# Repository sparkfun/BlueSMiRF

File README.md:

_**NOTE:** This version of the product has been retired from our catalog. However, we do have the [BlueSMIRF V2 with headers](https://www.sparkfun.com/products/23287) and the [BlueSMiRF V2 PTH version available](https://www.sparkfun.com/products/24113)!_

_Please check out some of these resources to see how other users are still hacking and improving on this version of the product._

* [SparkFun Forum](https://forum.sparkfun.com/)
* [Comments Here on GitHub](https://github.com/sparkfun/BlueSMiRF/issues)

BlueSMiRF
=========

<table class="table table-hover table-striped table-bordered">
  <tr align="center">
   <td></td>
   <td></td>
  </tr>
  <tr align="center">
    <td><a href="https://www.sparkfun.com/products/12582">Bluetooth BlueSMiRF Gold: RN-41 Module (WRL-12582)</a></td>
    <td><a href="https://www.sparkfun.com/products/12577">Bluetooth Modem-BlueSMiRF Silver: RN-42 module (WRL-12577)</a></td>
  </tr>
</table>

These Bluetooth wireless modems work as a TTL serial (RX/TX) pipe, as a replacement for serial cable connections. 

Repository Contents
-------------------
* **/Hardware** - All Eagle design files (.brd, .sch)

Documentation
--------------
* **[Hookup Guide](https://learn.sparkfun.com/tutorials/using-the-bluesmirf)** - Basic hookup guide for the BlueSMiRF and Bluetooth Mate.
* **[SparkFun 3D Model repo](https://github.com/sparkfun/3D_Models)** - 3D models of SparkFun products. 

Current Product Versions
------------------------
* [WRL-12582](https://www.sparkfun.com/products/12582)- BlueSMiRF Gold: RN-41 Module
* [WRL-12577](https://www.sparkfun.com/products/12577)- BlueSMiRF Silver: RN-42 Module

Retired Product Versions
------------------------
* [WRL-10269](https://www.sparkfun.com/products/10269)- BlueSMiRF Silver: RN-42 Module
* [WRL-10268](https://www.sparkfun.com/products/10268)- BlueSMiRF Gold: RN-41 Module v16
* [WRL-10938](https://www.sparkfun.com/products/10938)- BlueSMiRF HID: RN-42 module loaded with Human Interface Device firmware

License Information
-------------------
The hardware is released under [Creative Commons Share-alike 3.0](http://creativecommons.org/licenses/by-sa/3.0/).

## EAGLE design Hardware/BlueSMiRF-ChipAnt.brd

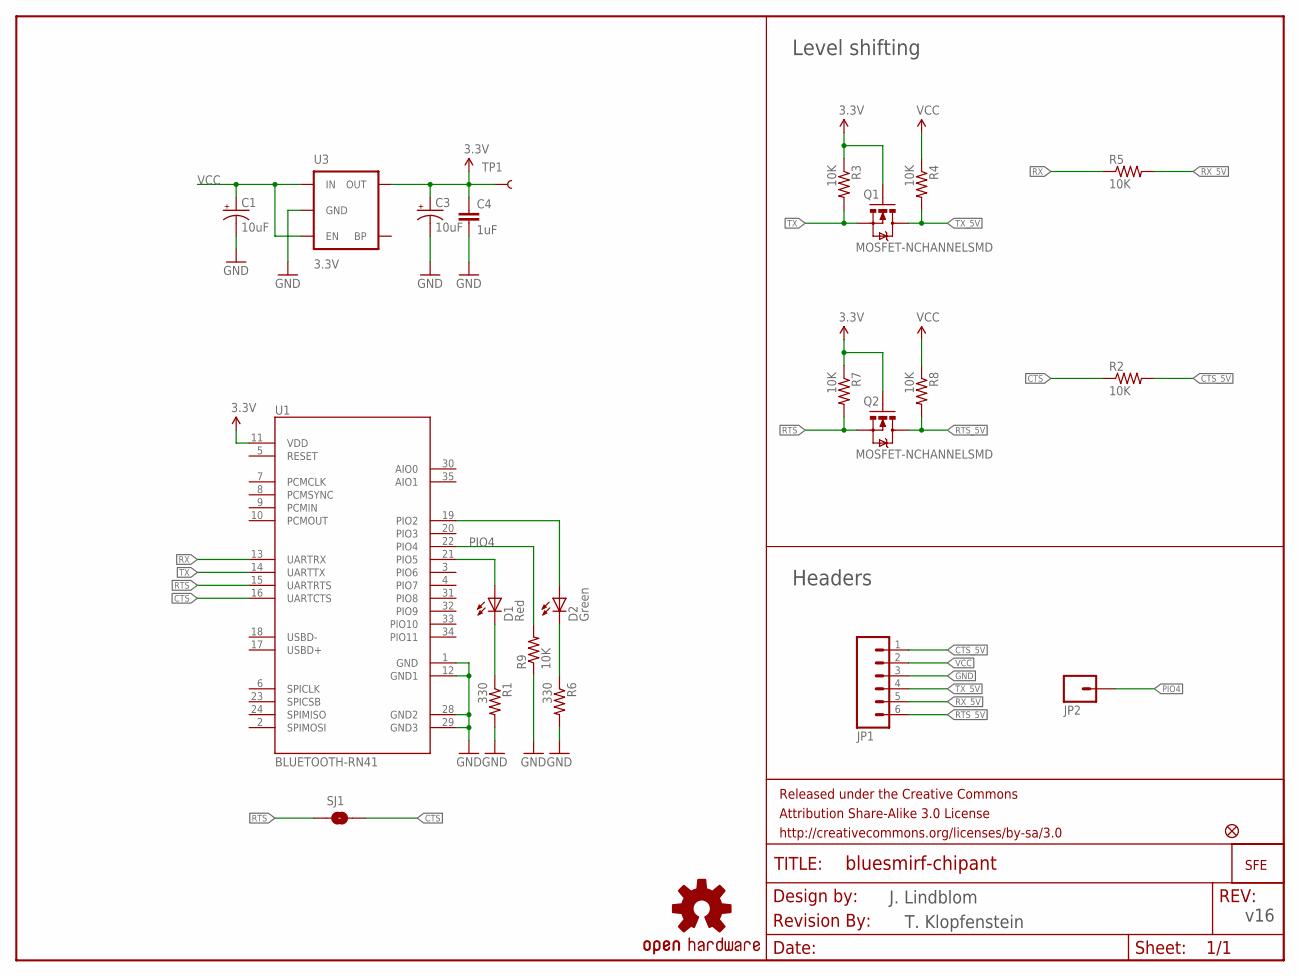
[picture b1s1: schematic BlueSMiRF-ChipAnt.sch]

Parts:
C1, C3: 10uF; EIA3216
C4: 1uF; 0603-CAP
D1: Red; LED-0603
D2: Green; LED-0603
FRAME1: FRAME-LETTER; CREATIVE_COMMONS
JP1: M06SIP; 1X06
JP2: M01SMDNS; 1X01NS
JP4: FIDUCIAL1X2; FIDUCIAL-1X2
LOGO1: OSHW-LOGOS; OSHW-LOGO-S
Q1, Q2: MOSFET-NCHANNELSMD; SOT23-3
R1, R6: 330; 0603-RES
R2, R3, R4, R5, R7, R8, R9: 10K; 0603-RES
SJ1: SOLDERJUMPERNO; SJ_2S-NO
TP1: TEST-POINT3X5; PAD.03X.05
U1: BLUETOOTH-RN41; RN41
U3: 3.3V; SOT23-5
U$1: LOGO-SFENEW; SFE-NEW-WEBLOGO
U$2: REVISION

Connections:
3.3V: C3.A (+), C4.1, Q1.1 (G), Q2.1 (G), R3.1, R7.1, TP1.P$1, U1.11 (VDD), U3.5 (OUT)
CTS: R2.1, SJ1.2, U1.16 (UARTCTS)
CTS_5V: JP1.1, R2.2
D1: D1.C, R1.1
D2: D2.C, R6.1
GND: C1.C (-), C3.C (-), C4.2, JP1.3, R1.2, R6.2, R9.1, U1.1 (GND), U1.12 (GND1), U1.28 (GND2), U1.29 (GND3), U3.2 (GND)
unnamed: D1.A, U1.21 (PIO5)
unnamed: D2.A, U1.19 (PIO2)
PIO4: JP2.1, R9.2, U1.22 (PIO4)
RTS: Q2.2 (S), R7.2, SJ1.1, U1.15 (UARTRTS)
RTS_5V: JP1.6, Q2.3 (D), R8.2
RX: R5.1, U1.13 (UARTRX)
RX_5V: JP1.5, R5.2
TX: Q1.2 (S), R3.2, U1.14 (UARTTX)
TX_5V: JP1.4, Q1.3 (D), R4.2
VCC: C1.A (+), JP1.2, R4.1, R8.1, U3.1 (IN), U3.3 (EN)

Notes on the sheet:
Level shifting
Headers
J. Lindblom
v16
T. Klopfenstein

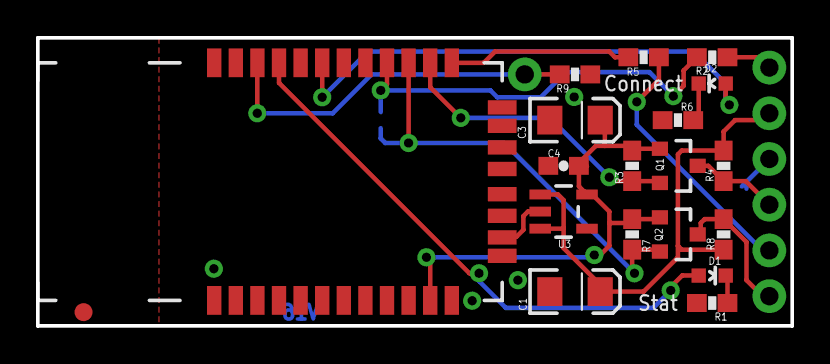
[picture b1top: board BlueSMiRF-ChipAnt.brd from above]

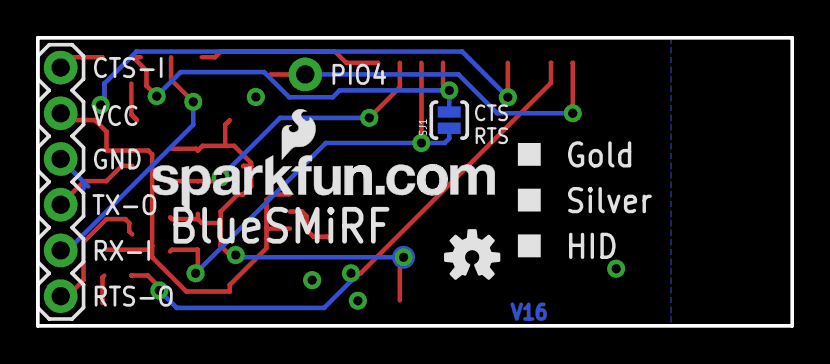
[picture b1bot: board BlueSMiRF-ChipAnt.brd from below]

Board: 2 copper layers, 41.9 x 16.0 mm, 27 parts (5 on the bottom side), 16 nets.

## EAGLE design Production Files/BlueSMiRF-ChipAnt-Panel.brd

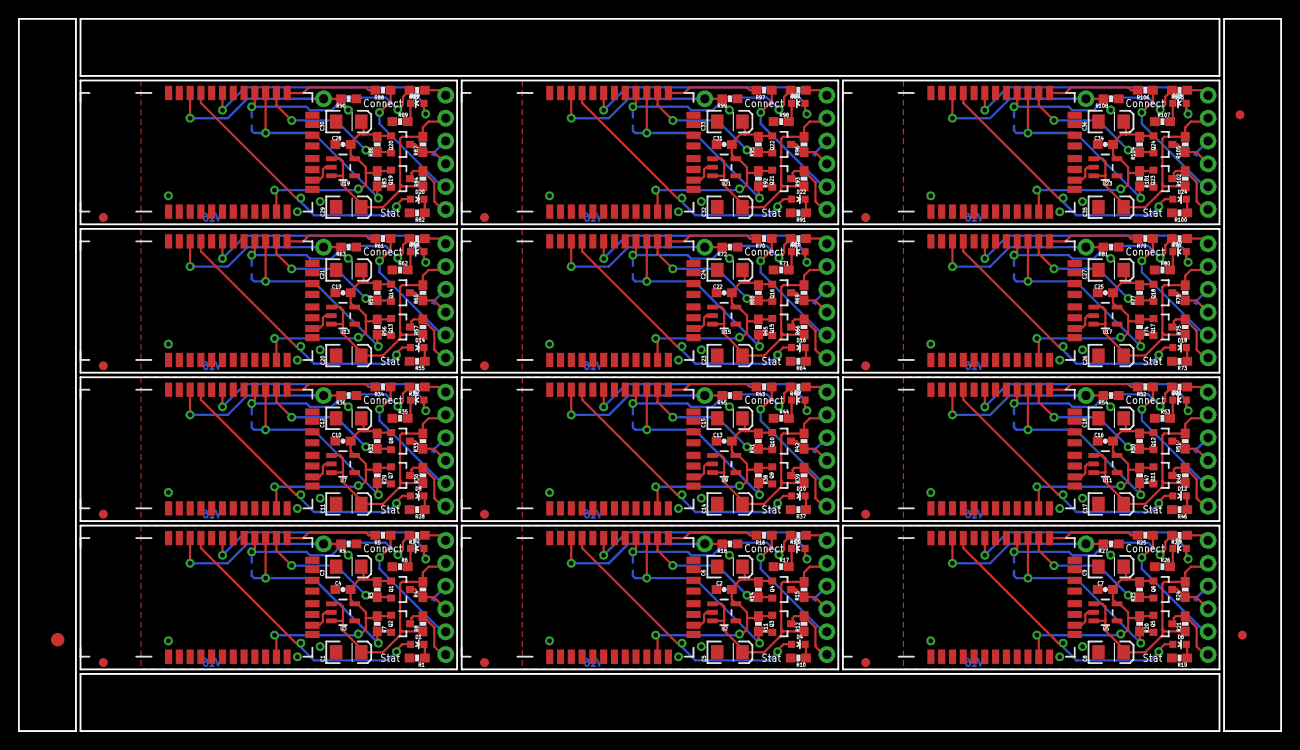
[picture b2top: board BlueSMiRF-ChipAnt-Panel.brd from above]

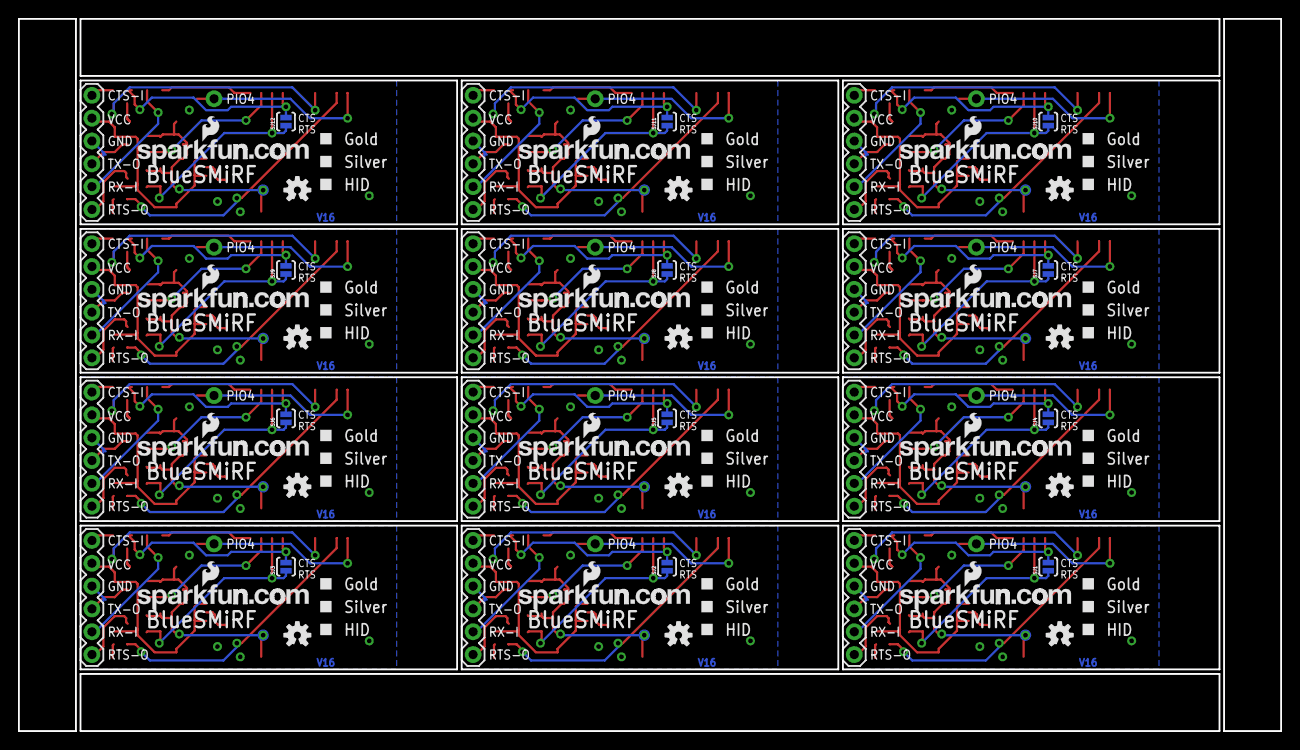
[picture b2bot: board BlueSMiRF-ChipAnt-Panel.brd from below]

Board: 2 copper layers, 140.5 x 79.2 mm, 303 parts (60 on the bottom side), 192 nets.

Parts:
C1, C3, C5, C6, C8, C9, C11, C12, C14, C15, C17, C18, C20, C21, C23, C24, C26, C27, C29, C30, C32, C33, C35, C36: 10uF; EIA3216
C2, C4, C7, C10, C13, C16, C19, C22, C25, C28, C31, C34: 1uF; 0603-CAP
D1, D4, D6, D8, D10, D12, D14, D16, D18, D20, D22, D24: Red; LED-0603
D2, D3, D5, D7, D9, D11, D13, D15, D17, D19, D21, D23: Green; LED-0603
E$1: FIDUCIAL-1.5X3
E$4, E$6: FIDUCIAL-1X2
JP1, JP3, JP7, JP10, JP13, JP16, JP19, JP22, JP25, JP28, JP31, JP34: 1X06
JP2, JP5, JP8, JP11, JP14, JP17, JP20, JP23, JP26, JP29, JP32, JP35: M01SMDNS; 1X01NS
JP4, JP6, JP9, JP12, JP15, JP18, JP21, JP24, JP27, JP30, JP33, JP36: FIDUCIAL1X2; FIDUCIAL-1X2
LOGO1, LOGO2, LOGO3, LOGO4, LOGO5, LOGO6, LOGO7, LOGO8, LOGO9, LOGO10, LOGO11, LOGO12: OSHW-LOGOS; OSHW-LOGO-S
Q1, Q2, Q3, Q4, Q5, Q6, Q7, Q8, Q9, Q10, Q11, Q12, Q13, Q14, Q15, Q16, Q17, Q18, Q19, Q20, Q21, Q22, Q23, Q24: MOSFET-NCHANNELSMD; SOT23-3
R1, R6, R10, R17, R19, R26, R28, R35, R37, R44, R46, R53, R55, R62, R64, R71, R73, R80, R82, R89, R91, R98, R100, R107: 330; 0603-RES
R2, R3, R4, R5, R7, R8, R9, R11, R12, R13, R14, R15, R16, R18, R20, R21, R22, R23, R24, R25, R27, R29, R30, R31, R32, R33, R34, R36, R38, R39, R40, R41, R42, R43, R45, R47, R48, R49, R50, R51, R52, R54, R56, R57, R58, R59, R60, R61, R63, R65, R66, R67, R68, R69, R70, R72, R74, R75, R76, R77, R78, R79, R81, R83, R84, R85, R86, R87, R88, R90, R92, R93, R94, R95, R96, R97, R99, R101, R102, R103, R104, R105, R106, R108: 10K; 0603-RES
SJ1, SJ2, SJ3, SJ4, SJ5, SJ6, SJ7, SJ8, SJ9, SJ10, SJ11, SJ12: SOLDERJUMPERNO; SJ_2S-NO
TP1, TP2, TP3, TP4, TP5, TP6, TP7, TP8, TP9, TP10, TP11, TP12: PAD.03X.05
U1, U4, U6, U8, U10, U12, U14, U16, U18, U20, U22, U24: BLUETOOTH-RN41; RN41
U2, U3, U5, U7, U9, U11, U13, U15, U17, U19, U21, U23: 3.3V; SOT23-5
U$1, U$2, U$3, U$4, U$5, U$6, U$7, U$8, U$9, U$10, U$11, U$12: LOGO-SFENEW; SFE-NEW-WEBLOGO

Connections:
3.3V: C3.A, C4.1, Q1.1, Q2.1, R3.1, R7.1, TP1.P$1, U1.11, U3.5
3.3V1: C2.1, C6.A, Q3.1, Q4.1, R11.1, R14.1, TP2.P$1, U2.5, U4.11
3.3V2: C7.1, C9.A, Q5.1, Q6.1, R20.1, R23.1, TP3.P$1, U5.5, U6.11
3.3V3: C10.1, C12.A, Q7.1, Q8.1, R29.1, R32.1, TP4.P$1, U7.5, U8.11
3.3V4: C13.1, C15.A, Q9.1, Q10.1, R38.1, R41.1, TP5.P$1, U9.5, U10.11
3.3V5: C16.1, C18.A, Q11.1, Q12.1, R47.1, R50.1, TP6.P$1, U11.5, U12.11
3.3V6: C19.1, C21.A, Q13.1, Q14.1, R56.1, R59.1, TP7.P$1, U13.5, U14.11
3.3V7: C22.1, C24.A, Q15.1, Q16.1, R65.1, R68.1, TP8.P$1, U15.5, U16.11
3.3V8: C25.1, C27.A, Q17.1, Q18.1, R74.1, R77.1, TP9.P$1, U17.5, U18.11
3.3V9: C28.1, C30.A, Q19.1, Q20.1, R83.1, R86.1, TP10.P$1, U19.5, U20.11
3.3V10: C31.1, C33.A, Q21.1, Q22.1, R92.1, R95.1, TP11.P$1, U21.5, U22.11
3.3V11: C34.1, C36.A, Q23.1, Q24.1, R101.1, R104.1, TP12.P$1, U23.5, U24.11
CTS: R2.1, SJ1.2, U1.16
CTS1: R13.1, SJ2.2, U4.16
CTS2: R22.1, SJ3.2, U6.16
CTS3: R31.1, SJ4.2, U8.16
CTS4: R40.1, SJ5.2, U10.16
CTS5: R49.1, SJ6.2, U12.16
CTS6: R58.1, SJ7.2, U14.16
CTS7: R67.1, SJ8.2, U16.16
CTS8: R76.1, SJ9.2, U18.16
CTS9: R85.1, SJ10.2, U20.16
CTS10: R94.1, SJ11.2, U22.16
CTS11: R103.1, SJ12.2, U24.16
CTS_5V: JP1.1, R2.2
CTS_5V1: JP3.1, R13.2
CTS_5V2: JP7.1, R22.2
CTS_5V3: JP10.1, R31.2
CTS_5V4: JP13.1, R40.2
CTS_5V5: JP16.1, R49.2
CTS_5V6: JP19.1, R58.2
CTS_5V7: JP22.1, R67.2
CTS_5V8: JP25.1, R76.2
CTS_5V9: JP28.1, R85.2
CTS_5V10: JP31.1, R94.2
CTS_5V11: JP34.1, R103.2
D1: D1.C, R1.1
D2: D2.C, R6.1
D3: D4.C, R10.1
D4: D3.C, R17.1
D5: D6.C, R19.1
D6: D5.C, R26.1
D7: D8.C, R28.1
D8: D7.C, R35.1
D9: D10.C, R37.1
D10: D9.C, R44.1
D11: D12.C, R46.1
D12: D11.C, R53.1
D13: D14.C, R55.1
D14: D13.C, R62.1
D15: D16.C, R64.1
D16: D15.C, R71.1
D17: D18.C, R73.1
D18: D17.C, R80.1
D19: D20.C, R82.1
D20: D19.C, R89.1
D21: D22.C, R91.1
D22: D21.C, R98.1
D23: D24.C, R100.1
D24: D23.C, R107.1
GND: C1.C, C3.C, C4.2, JP1.3, R1.2, R6.2, R9.1, U1.1, U1.12, U1.28, U1.29, U3.2
GND1: C2.2, C5.C, C6.C, JP3.3, R10.2, R17.2, R18.1, U2.2, U4.1, U4.12, U4.28, U4.29
GND2: C7.2, C8.C, C9.C, JP7.3, R19.2, R26.2, R27.1, U5.2, U6.1, U6.12, U6.28, U6.29
GND3: C10.2, C11.C, C12.C, JP10.3, R28.2, R35.2, R36.1, U7.2, U8.1, U8.12, U8.28, U8.29
GND4: C13.2, C14.C, C15.C, JP13.3, R37.2, R44.2, R45.1, U9.2, U10.1, U10.12, U10.28, U10.29
GND5: C16.2, C17.C, C18.C, JP16.3, R46.2, R53.2, R54.1, U11.2, U12.1, U12.12, U12.28, U12.29
GND6: C19.2, C20.C, C21.C, JP19.3, R55.2, R62.2, R63.1, U13.2, U14.1, U14.12, U14.28, U14.29
GND7: C22.2, C23.C, C24.C, JP22.3, R64.2, R71.2, R72.1, U15.2, U16.1, U16.12, U16.28, U16.29
GND8: C25.2, C26.C, C27.C, JP25.3, R73.2, R80.2, R81.1, U17.2, U18.1, U18.12, U18.28, U18.29
GND9: C28.2, C29.C, C30.C, JP28.3, R82.2, R89.2, R90.1, U19.2, U20.1, U20.12, U20.28, U20.29
GND10: C31.2, C32.C, C33.C, JP31.3, R91.2, R98.2, R99.1, U21.2, U22.1, U22.12, U22.28, U22.29
GND11: C34.2, C35.C, C36.C, JP34.3, R100.2, R107.2, R108.1, U23.2, U24.1, U24.12, U24.28, U24.29
unnamed: D1.A, U1.21
unnamed: D2.A, U1.19
unnamed: D4.A, U4.21
unnamed: D3.A, U4.19
unnamed: D6.A, U6.21
unnamed: D5.A, U6.19
unnamed: D8.A, U8.21
unnamed: D7.A, U8.19
unnamed: D10.A, U10.21
unnamed: D9.A, U10.19
unnamed: D12.A, U12.21
unnamed: D11.A, U12.19
unnamed: D14.A, U14.21
unnamed: D13.A, U14.19
unnamed: D16.A, U16.21
unnamed: D15.A, U16.19
unnamed: D18.A, U18.21
unnamed: D17.A, U18.19
unnamed: D20.A, U20.21
unnamed: D19.A, U20.19
unnamed: D22.A, U22.21
unnamed: D21.A, U22.19
unnamed: D24.A, U24.21
unnamed: D23.A, U24.19
PIO1: JP5.1, R18.2, U4.22
PIO2: JP8.1, R27.2, U6.22
PIO3: JP11.1, R36.2, U8.22
PIO4: JP2.1, R9.2, U1.22
PIO5: JP14.1, R45.2, U10.22
PIO6: JP17.1, R54.2, U12.22
PIO7: JP20.1, R63.2, U14.22
PIO8: JP23.1, R72.2, U16.22
PIO9: JP26.1, R81.2, U18.22
PIO10: JP29.1, R90.2, U20.22
PIO11: JP32.1, R99.2, U22.22
PIO12: JP35.1, R108.2, U24.22
RTS: Q2.2, R7.2, SJ1.1, U1.15
RTS1: Q3.2, R11.2, SJ2.1, U4.15
RTS2: Q5.2, R20.2, SJ3.1, U6.15
RTS3: Q7.2, R29.2, SJ4.1, U8.15
RTS4: Q9.2, R38.2, SJ5.1, U10.15
RTS5: Q11.2, R47.2, SJ6.1, U12.15
RTS6: Q13.2, R56.2, SJ7.1, U14.15
RTS7: Q15.2, R65.2, SJ8.1, U16.15
RTS8: Q17.2, R74.2, SJ9.1, U18.15
RTS9: Q19.2, R83.2, SJ10.1, U20.15
RTS10: Q21.2, R92.2, SJ11.1, U22.15
RTS11: Q23.2, R101.2, SJ12.1, U24.15
RTS_5V: JP1.6, Q2.3, R8.2
RTS_5V1: JP3.6, Q3.3, R12.2
RTS_5V2: JP7.6, Q5.3, R21.2
RTS_5V3: JP10.6, Q7.3, R30.2
RTS_5V4: JP13.6, Q9.3, R39.2
RTS_5V5: JP16.6, Q11.3, R48.2
RTS_5V6: JP19.6, Q13.3, R57.2
RTS_5V7: JP22.6, Q15.3, R66.2
RTS_5V8: JP25.6, Q17.3, R75.2
RTS_5V9: JP28.6, Q19.3, R84.2
RTS_5V10: JP31.6, Q21.3, R93.2
RTS_5V11: JP34.6, Q23.3, R102.2
RX: R5.1, U1.13
RX1: R16.1, U4.13
RX2: R25.1, U6.13
RX3: R34.1, U8.13
RX4: R43.1, U10.13
RX5: R52.1, U12.13
RX6: R61.1, U14.13
RX7: R70.1, U16.13
RX8: R79.1, U18.13
RX9: R88.1, U20.13
RX10: R97.1, U22.13
RX11: R106.1, U24.13
RX_5V: JP1.5, R5.2
RX_5V1: JP3.5, R16.2
RX_5V2: JP7.5, R25.2
RX_5V3: JP10.5, R34.2
RX_5V4: JP13.5, R43.2
RX_5V5: JP16.5, R52.2
RX_5V6: JP19.5, R61.2
RX_5V7: JP22.5, R70.2
RX_5V8: JP25.5, R79.2
RX_5V9: JP28.5, R88.2
RX_5V10: JP31.5, R97.2
RX_5V11: JP34.5, R106.2
TX: Q1.2, R3.2, U1.14
TX1: Q4.2, R14.2, U4.14
TX2: Q6.2, R23.2, U6.14
TX3: Q8.2, R32.2, U8.14
TX4: Q10.2, R41.2, U10.14
TX5: Q12.2, R50.2, U12.14
TX6: Q14.2, R59.2, U14.14
TX7: Q16.2, R68.2, U16.14
TX8: Q18.2, R77.2, U18.14
TX9: Q20.2, R86.2, U20.14
TX10: Q22.2, R95.2, U22.14
TX11: Q24.2, R104.2, U24.14
TX_5V: JP1.4, Q1.3, R4.2
TX_5V1: JP3.4, Q4.3, R15.2
TX_5V2: JP7.4, Q6.3, R24.2
TX_5V3: JP10.4, Q8.3, R33.2
TX_5V4: JP13.4, Q10.3, R42.2
TX_5V5: JP16.4, Q12.3, R51.2
TX_5V6: JP19.4, Q14.3, R60.2
TX_5V7: JP22.4, Q16.3, R69.2
TX_5V8: JP25.4, Q18.3, R78.2
TX_5V9: JP28.4, Q20.3, R87.2
TX_5V10: JP31.4, Q22.3, R96.2
TX_5V11: JP34.4, Q24.3, R105.2
VCC: C1.A, JP1.2, R4.1, R8.1, U3.1, U3.3
VCC1: C5.A, JP3.2, R12.1, R15.1, U2.1, U2.3
VCC2: C8.A, JP7.2, R21.1, R24.1, U5.1, U5.3
VCC3: C11.A, JP10.2, R30.1, R33.1, U7.1, U7.3
VCC4: C14.A, JP13.2, R39.1, R42.1, U9.1, U9.3
VCC5: C17.A, JP16.2, R48.1, R51.1, U11.1, U11.3
VCC6: C20.A, JP19.2, R57.1, R60.1, U13.1, U13.3
VCC7: C23.A, JP22.2, R66.1, R69.1, U15.1, U15.3
VCC8: C26.A, JP25.2, R75.1, R78.1, U17.1, U17.3
VCC9: C29.A, JP28.2, R84.1, R87.1, U19.1, U19.3
VCC10: C32.A, JP31.2, R93.1, R96.1, U21.1, U21.3
VCC11: C35.A, JP34.2, R102.1, R105.1, U23.1, U23.3

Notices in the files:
parts and their libraries:
SparkFun-Aesthetics: Licensing: CC v3.0 Share-Alike You are welcome to use this library for commercial purposes.
SparkFun-Aesthetics: Released under the Creative Commons Attribution Share-Alike 3.0 License
SparkFun-Aesthetics: Released under the Creative Commons
